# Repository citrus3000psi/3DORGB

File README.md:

# 3DORGB
RGB Project for most 3DO consoles.

Copyright 2020 Daniel Kunz

Permission is hereby granted, free of charge, to any person obtaining a copy of this software and associated documentation files (the "Software"), to deal in the Software without restriction, including without limitation the rights to use, copy, modify, merge, publish, distribute, sublicense, and/or sell copies of the Software, and to permit persons to whom the Software is furnished to do so, subject to the following conditions:

The above copyright notice and this permission notice shall be included in all copies or substantial portions of the Software.

THE SOFTWARE IS PROVIDED "AS IS", WITHOUT WARRANTY OF ANY KIND, EXPRESS OR IMPLIED, INCLUDING BUT NOT LIMITED TO THE WARRANTIES OF MERCHANTABILITY, FITNESS FOR A PARTICULAR PURPOSE AND NONINFRINGEMENT. IN NO EVENT SHALL THE AUTHORS OR COPYRIGHT HOLDERS BE LIABLE FOR ANY CLAIM, DAMAGES OR OTHER LIABILITY, WHETHER IN AN ACTION OF CONTRACT, TORT OR OTHERWISE, ARISING FROM, OUT OF OR IN CONNECTION WITH THE SOFTWARE OR THE USE OR OTHER DEALINGS IN THE SOFTWARE.

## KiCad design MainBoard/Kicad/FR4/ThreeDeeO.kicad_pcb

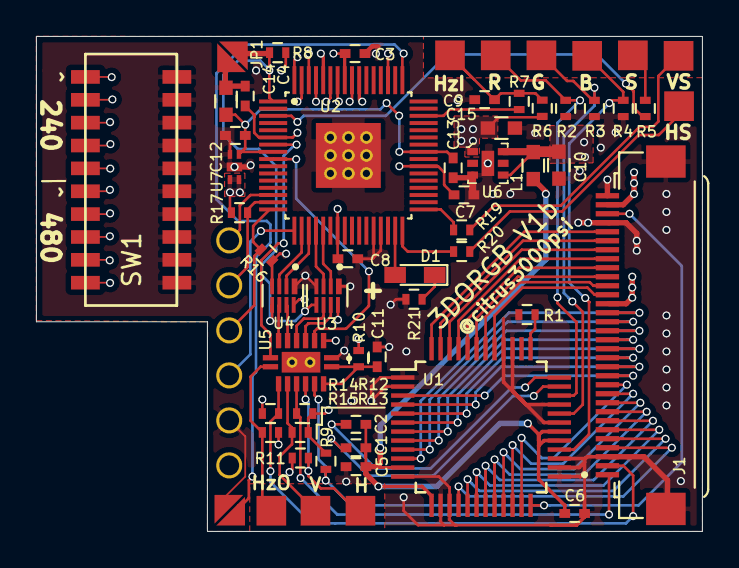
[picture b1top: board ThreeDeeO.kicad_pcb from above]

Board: 4 copper layers, 37.0 x 27.5 mm, 59 parts (0 on the bottom side), 78 nets.

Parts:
C1, C2, C3, C4, C5, C6, C7, C8, C9, C11, C12, C13: .1u; C_0402
C10, C14, C15: 10u; C_0603
D1: LED_Small; LED_0603_HandSoldering
J1: 3-1775333-2; TE_3-1775333-2
J2: JTAG; SPI_PADS
J3, J8, J9, J10, J11, J13: S; small_pad
J4: R; small_pad
J5: G; small_pad
J6, J12: B; small_pad
JP1, JP2: Jumper_NO_Small; Jumper
L1: 10ohm; C_0603
R1: 536; R_0402
R2, R3, R4: 75; R_0402
R5, R7, R16: 1K; R_0402
R6, R8, R17: 10K; R_0402
R9, R11, R12, R13, R14, R15: 523; R_0402
R10: 200K; R_0402
R19, R20: 50; R_0402
R21: 330; R_0402
SW1: SW_DIP_x10; SWDIP10
U1: ADV7125-lqfp48; TQFP-48_7x7mm_Pitch0.5mm
U2: 5M160ZE64I5N; QFP40P900X900X120-65N
U3, U4: 7WB383MUTAG; SON40P180X120X55-8N
U5: NVT2006BQ_115; QFN50P250X350X100-17N
U6: TPS73733DRVR; UDFN-6-1EP_2x2mm
U7: MIC94310

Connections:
+5V: C1.2, C2.2, C5.1, C6.1, L1.1, U1.11, U1.13, U1.29, U1.30
/240B0: SW1.11, U2.60
/240B1: SW1.12, U2.62
/240B2: SW1.13, U2.64
/240B3: SW1.14, U2.51
/240B4: SW1.15, U2.55
/480B0: SW1.16, U2.56
/480B1: SW1.17, U2.58
/480B2: SW1.18, U2.59
/480B3: SW1.19, U2.61
/480B4: SW1.20, U2.63
/+1.8: C12.1, C13.1, C14.1, U2.8, U2.41, U7.1
/+3.3: C3.1, C4.1, C7.1, C8.1, C15.1, J2.1, R6.2, R8.2, R17.2, U2.6, U2.23, U2.39, U2.57, U3.8, U4.8, U5.2, U6.1, U7.3, U7.4
/+5: C10.1, J1.20, J1.31, L1.2, R9.2, R10.1, R11.2, R12.2, R13.2, R14.2, R15.2, U6.4, U6.6
/B0: J1.4, U1.16
/B1: J1.5, U1.17
/B2: J1.6, U1.18
/B3: J1.7, U1.19
/B4: J1.8, U1.20
/B5: J1.9, U1.21
/B6: J1.10, U1.22
/B7: J1.11, U1.23
/BLUE: J6.1, R4.2, U1.28
/CLK12: J1.30, R9.1, U1.24, U5.14
/CLK12_3.3: U2.9, U5.3
/CSYNC: J3.1, R5.1
/EX: JP1.1, R8.1, U2.1, U3.5, U4.5
/G0: J1.12, U1.3
/G1: J1.13, U1.4
/G2: J1.14, U1.5
/G3: J1.15, U1.6
/G4: J1.16, U1.7
/G5: J1.17, U1.8
/G6: J1.18, U1.9
/G7: J1.19, U1.10
/GREEN: J5.1, R3.2, U1.32
/HOUT: J8.1, R11.1, U5.13
/HOUT_3.3: U2.20, U3.3
/HSYNC: J1.1, R12.1, U5.12
/HSYNC_3.3: U2.21, U3.2
/HVGA: R19.1, U2.33
/INTERLACE: J12.1, R15.1, U5.9
/INTERLACE_3.3: U2.7, U5.8
/INTERLACE_SW: R7.1, U2.46
/R0: J1.21, U1.41
/R1: J1.22, U1.42
/R2: J1.23, U1.43
/R3: J1.24, U1.44
/R4: J1.25, U1.45
/R5: J1.26, U1.46
/R6: J1.27, U1.47
/R7: J1.28, U1.48
/RED: J4.1, R2.2, U1.34
/TCK: J2.4, R16.1, U2.16
/TDI: J2.5, R17.1, U2.15
/TDO: J2.3, U2.17
/TMS: J2.6, U2.14
/VOUT: J9.1, R13.1, U5.11
/VOUT_3.3: U2.18, U4.3
/VSYNC: J1.2, R14.1, U5.10
/VSYNC_3.3: U2.19, U4.2
/VVGA: R20.1, U2.32
GND: C3.2, C4.2, C5.2, C6.2, C7.2, C8.2, C9.1, C10.2, C11.1, C12.2, C13.2, C14.2, C15.2, J1.3, J1.29, J1.32, J1.S1, J1.S2, J2.2, JP1.2, JP2.2, R1.1, R2.1, R3.1, R4.1, R16.2, R21.2, SW1.1, SW1.2, SW1.3, SW1.4, SW1.5, SW1.6, SW1.7, SW1.8, SW1.9, SW1.10, U1.1, U1.2, U1.12, U1.14, U1.15, U1.25, U1.26, U1.27, U1.31, U1.33, U1.39, U1.40, U2.28, U2.29, U2.65, U3.1, U3.4, U4.1, U4.4, U5.1, U6.3, U7.2
unnamed: C1.1, U1.35
unnamed: C2.1, U1.36
unnamed: C9.2, J11.1, R6.1, R7.2
unnamed: C11.2, R10.2, U5.15, U5.16
unnamed: D1.1, R21.1
unnamed: D1.2, U2.31
unnamed: J10.1, R19.2
unnamed: J13.1, R20.2
unnamed: JP2.1, U2.49
unnamed: R1.2, U1.37
unnamed: R5.2, U2.3
unnamed: U3.6, U5.5
unnamed: U3.7, U5.4
unnamed: U4.6, U5.7
unnamed: U4.7, U5.6

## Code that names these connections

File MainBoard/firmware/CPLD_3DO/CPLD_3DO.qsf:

# -------------------------------------------------------------------------- #
#
# Copyright (C) 2017  Intel Corporation. All rights reserved.
# Your use of Intel Corporation's design tools, logic functions 
# and other software and tools, and its AMPP partner logic 
# functions, and any output files from any of the foregoing 
# (including device programming or simulation files), and any 
# associated documentation or information are expressly subject 
# to the terms and conditions of the Intel Program License 
# Subscription Agreement, the Intel Quartus Prime License Agreement,
# the Intel FPGA IP License Agreement, or other applicable license
# agreement, including, without limitation, that your use is for
# the sole purpose of programming logic devices manufactured by
# Intel and sold by Intel or its authorized distributors.  Please
# refer to the applicable agreement for further details.
#
# -------------------------------------------------------------------------- #
#
# Quartus Prime
# Version 17.1.0 Build 590 10/25/2017 SJ Lite Edition
# Date created = 14:16:42  August 07, 2019
#
# -------------------------------------------------------------------------- #
#
# Notes:
#
# 1) The default values for assignments are stored in the file:
#		CPLD_3DO_assignment_defaults.qdf
#    If this file doesn't exist, see file:
#		assignment_defaults.qdf
#
# 2) Altera recommends that you do not modify this file. This
#    file is updated automatically by the Quartus Prime software
#    and any changes you make may be lost or overwritten.
#
# -------------------------------------------------------------------------- #


set_global_assignment -name FAMILY "MAX V"
set_global_assignment -name DEVICE 5M160ZE64I5
set_global_assignment -name TOP_LEVEL_ENTITY CPLD_3DO
set_global_assignment -name ORIGINAL_QUARTUS_VERSION 17.1.0
set_global_assignment -name PROJECT_CREATION_TIME_DATE "14:16:42  AUGUST 07, 2019"
set_global_assignment -name LAST_QUARTUS_VERSION "17.1.0 Lite Edition"
set_global_assignment -name PROJECT_OUTPUT_DIRECTORY output_files
set_global_assignment -name MIN_CORE_JUNCTION_TEMP "-40"
set_global_assignment -name MAX_CORE_JUNCTION_TEMP 125
set_global_assignment -name ERROR_CHECK_FREQUENCY_DIVISOR "-1"
set_global_assignment -name VERILOG_FILE CPLD_3DO.v
set_global_assignment -name POWER_PRESET_COOLING_SOLUTION "NO HEAT SINK WITH STILL AIR"
set_global_assignment -name OPTIMIZATION_MODE "AGGRESSIVE PERFORMANCE"
set_global_assignment -name TIMEQUEST_MULTICORNER_ANALYSIS OFF
set_global_assignment -name NUM_PARALLEL_PROCESSORS ALL
set_global_assignment -name FIT_ATTEMPTS_TO_SKIP 0
set_global_assignment -name OPTIMIZE_POWER_DURING_FITTING "NORMAL COMPILATION"
set_global_assignment -name AUTO_PACKED_REGISTERS_MAX "MINIMIZE AREA WITH CHAINS"
set_global_assignment -name OPTIMIZE_TIMING "NORMAL COMPILATION"
set_global_assignment -name ROUTER_EFFORT_MULTIPLIER 2.0
set_global_assignment -name PHYSICAL_SYNTHESIS_EFFORT EXTRA
set_global_assignment -name MUX_RESTRUCTURE OFF
set_location_assignment PIN_9 -to clk12
set_location_assignment PIN_3 -to csync_o
set_location_assignment PIN_1 -to encoder
set_location_assignment PIN_21 -to hsync
set_location_assignment PIN_20 -to hsync_o
set_location_assignment PIN_46 -to interlace_in
set_location_assignment PIN_7 -to interlace_out
set_location_assignment PIN_19 -to vsync
set_location_assignment PIN_18 -to vsync_o
set_location_assignment PIN_33 -to hsync_o_VGA
set_location_assignment PIN_32 -to vsync_o_VGA
set_location_assignment PIN_31 -to led
set_location_assignment PIN_49 -to encoder_bt9103
set_instance_assignment -name WEAK_PULL_UP_RESISTOR ON -to encoder_bt9103
set_instance_assignment -name IO_STANDARD "3.3-V LVTTL" -to b0_240
set_location_assignment PIN_60 -to b0_240
set_location_assignment PIN_56 -to b0_480
set_location_assignment PIN_62 -to b1_240
set_location_assignment PIN_58 -to b1_480
set_location_assignment PIN_64 -to b2_240
set_location_assignment PIN_59 -to b2_480
set_location_assignment PIN_51 -to b3_240
set_location_assignment PIN_61 -to b3_480
set_location_assignment PIN_55 -to b4_240
set_location_assignment PIN_63 -to b4_480
set_instance_assignment -name WEAK_PULL_UP_RESISTOR ON -to b0_240
set_instance_assignment -name WEAK_PULL_UP_RESISTOR ON -to b0_480
set_instance_assignment -name WEAK_PULL_UP_RESISTOR ON -to b1_240
set_instance_assignment -name WEAK_PULL_UP_RESISTOR ON -to b1_480
set_instance_assignment -name WEAK_PULL_UP_RESISTOR ON -to b2_240
set_instance_assignment -name WEAK_PULL_UP_RESISTOR ON -to b2_480
set_instance_assignment -name WEAK_PULL_UP_RESISTOR ON -to b3_240
set_instance_assignment -name WEAK_PULL_UP_RESISTOR ON -to b3_480
set_instance_assignment -name WEAK_PULL_UP_RESISTOR ON -to b4_240
set_instance_assignment -name WEAK_PULL_UP_RESISTOR ON -to b4_480

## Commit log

2020-06-02 Files added
2020-06-02 Added firmware source
2020-07-02 Add MiniDin
2020-07-02 Update Gerber
2020-07-02 Add breakout
2020-07-08 Added correct BOM
2020-07-08 Minor updates
2020-07-08 Correct BOM
2020-07-08 Use tested gerbers from last run
2020-07-13 Removed R18 which is no longer in use
2020-07-13 added missing .mod files
2020-07-13 added another missing .mod file
2020-07-13 Added Missing LIBs
2020-10-16 Added 9pin gerbers
